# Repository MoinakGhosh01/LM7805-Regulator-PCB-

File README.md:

# LM7805 Voltage Regulator PCB

## Description
This project is a 12V to 5V linear voltage regulator designed using LM7805 in KiCad.

## Features
- Input: 7V–35V DC
- Output: 5V regulated
- Load: ~100mA
- Thermal copper pour for heat dissipation
- Screw terminal connectors

## Tools Used
- KiCad
- PCB Design & DRC

## Learning
- PCB layout and grounding
- Thermal management
- Limitations of SPICE simulation in KiCad

## Files
- Schematic (.kicad_sch)
- PCB Layout (.kicad_pcb)
- Project file (.kicad_pro)

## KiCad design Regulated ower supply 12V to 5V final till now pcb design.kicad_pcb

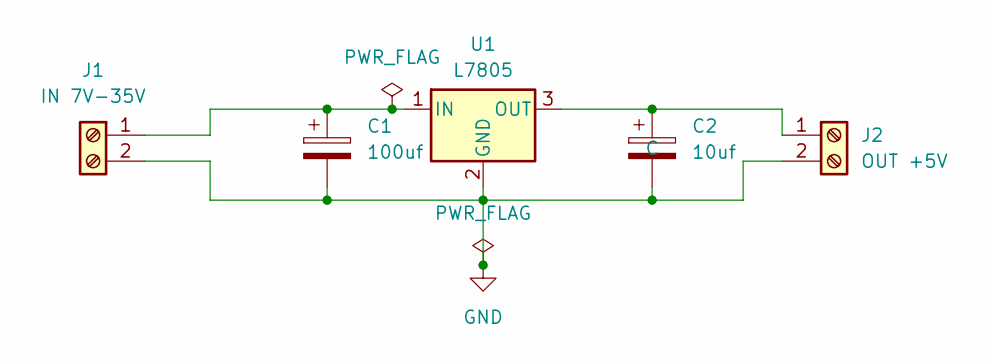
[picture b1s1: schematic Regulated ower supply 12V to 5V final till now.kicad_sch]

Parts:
C1: 100uf; CP_Radial_D6.3mm_P2.50mm
C2: 10uf; CP_Radial_D6.3mm_P2.50mm
J1: IN 7V-35V; Altech_AK300_1x02_P5.00mm_45-Degree
J2: OUT +5V; Altech_AK300_1x02_P5.00mm_45-Degree
U1: L7805; TO-252-3_TabPin4

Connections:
GND: C1.2, C2.2, J1.2, J2.2, U1.2 (GND)
unnamed: C1.1, J1.1, U1.1 (IN)
unnamed: C2.1, J2.1, U1.3 (OUT)

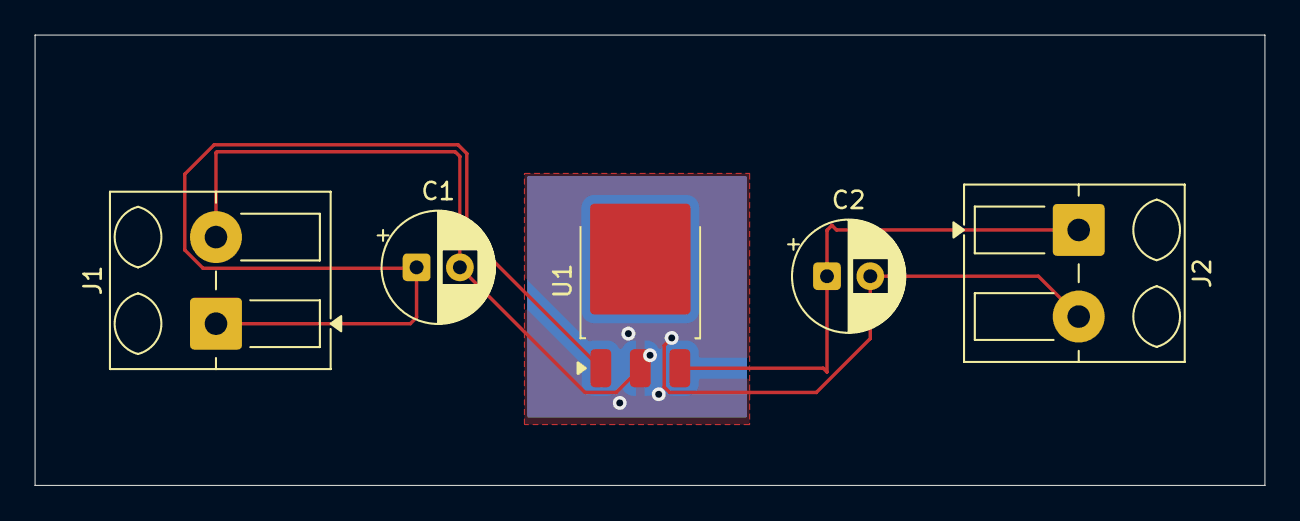
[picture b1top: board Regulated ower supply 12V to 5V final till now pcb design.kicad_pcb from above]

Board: 2 copper layers, 71.0 x 26.0 mm, 5 parts (0 on the bottom side), 3 nets.

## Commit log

2026-03-31 Add files via upload
    LM7805 PCB DESIGN IN KiCad.
2026-03-31 Initialize README with project information
    Added project details for LM7805 Voltage Regulator PCB.
